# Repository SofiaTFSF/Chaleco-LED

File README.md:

# Chaleco-LED

## Presentación 
#### Integrantes
  -Carlos David Manzanares Medina.
  
  -Sofia Nuñez Montenegro.
#### Materia 
   -Taller de Electrónica
#### Profesor 
   -Johnny German Cubides Castro
   
## ¿Qué es?

Este chaleco es una ergonómica prenda la cual tiene integrada un sistema de luces la cual puedes ser modificada por medio de una aplicación que cumple la función de mando segun sea la necesidad del ciclista, ya sea que el usuario de la bicicleta gire, frene, o requiera de algun tipo de ayuda.

## Planteamiento del problema

En la actualidad, la ciudad de Bogotá experimenta lamentablemente una elevada incidencia de accidentes involucrando ciclistas. Estos incidentes de tránsito se atribuyen a diversas causas, siendo una de ellas la insuficiente comunicación entre los usuarios de la vía. Con el objetivo de mitigar esta problemática, se pretende concebir y desarrollar un chaleco dotado de un sistema de señalización direccional. Este dispositivo tiene como finalidad comunicar de manera efectiva las intenciones del ciclista a otros conductores, ya sea al realizar giros, frenar o requerir asistencia. La implementación de dicho sistema se llevará a cabo mediante la conectividad inalámbrica con dispositivos móviles.

## Objetivo

Nuestro objetivo principal es ayudar a que los ciclistas sean mas visibles en la vía minimizando así lo mayor posible los accidentes de los usuarios de este medio de transporte, este chaleco ayudará a que los ciclistas sean mas visibles especialmente en la noche por medio de un sistema de direccionales que permitirá comunicar los movimientos y prevenir cualquier inconveniente o accidente.

Se busca proporcionar información útil a otros conductores de vehiculos automatizados los cuales usan un sistema de señalización para indicar si voltean a la derecha, la izquierda o si están frenando, se incorporará este sistema por medio de un mando (aplicación) y un chaleco para ciclistas y así reducir los accidentes en la vía y por consiguiente reducir las muertes de ciclistas atropellados las cuales han aumentado en los últimos años.

Adicional a esto se espera promover el uso de la bicicleta como medio principal de transporte pues al mejorar la seguridad (unas de las razones por las cuales muchas personas no la usan) mas personas se sentiran atraidas por un medio de transporte que no solo mejorará su salud fisica y mental si no tambien ayudara a promover actos para preservar el medio ambiente, mitigando aunque sea un poco la emision dioxido de carbono.

## proceso

El primer paso en este proyecto consistió en identificar la problemática de los accidentes viales sufridos por ciclistas, particularmente debido a la colisión con vehículos automatizados, como automóviles, camionetas o autobuses. Con el objetivo de mitigar estos incidentes, se concibió la idea de incorporar un sistema de direccionales para permitir la comunicación entre ciclistas y la toma de decisiones anticipadas.

El proceso de desarrollo se centró en la creación de un diseño ergonómico que ofreciera comodidad a los ciclistas durante su manejo. Inicialmente, se abordó la implementación de luces, consideradas como un componente crucial para la visibilidad y seguridad. Estas luces fueron cortadas y conectadas de manera estratégica para alinearse con los conceptos y perspectivas de diseño, priorizando la excelencia tanto en estética como en la experiencia del usuario. La programación subsiguiente permitió que estas luces formaran símbolos legibles y universales para realizar señales claras.

El siguiente paso se enfocó en el diseño de la PCB (Placa de Circuito), que posibilitaría la desconexión de las luces de una fuente innamovible, garantizando así la movilidad del ciclista. La PCB incluye componentes como resistencias, el conector de luces, un jack, un microcontrolador (ESP32) y un portapilas. La fase de implementación abarcó la soldadura y conexión de los componentes, resolviendo eficientemente las posibles fallas presentadas durante este proceso. Este enfoque integral permitió avanzar de manera significativa hacia la materialización de una solución efectiva y segura para los ciclistas en el contexto del tráfico vial automatizado.

## Conclusiones 

Aunque el proceso no estuvo exento de desafíos, caracterizado por fluctuaciones y contratiempos, la culminación exitosa del proyecto se atribuye a diversos factores. La colaboración y orientación proporcionadas por el docente desempeñaron un papel fundamental, brindando dirección y apoyo técnico a lo largo de todas las etapas. Las herramientas facilitadas por el docente también desempeñaron un papel crucial al dotar al equipo de los recursos necesarios para abordar las complejidades del proyecto.

La resolución efectiva de problemas de última hora resultó ser un elemento determinante en el éxito final del emprendimiento. Este logro fue posible gracias al compromiso y dedicación de los miembros del equipo, quienes demostraron una actitud perseverante frente a los desafíos surgidos durante el desarrollo del chaleco funcional. La capacidad de adaptación y la disposición para superar obstáculos fueron cualidades clave que caracterizaron el desempeño del equipo.

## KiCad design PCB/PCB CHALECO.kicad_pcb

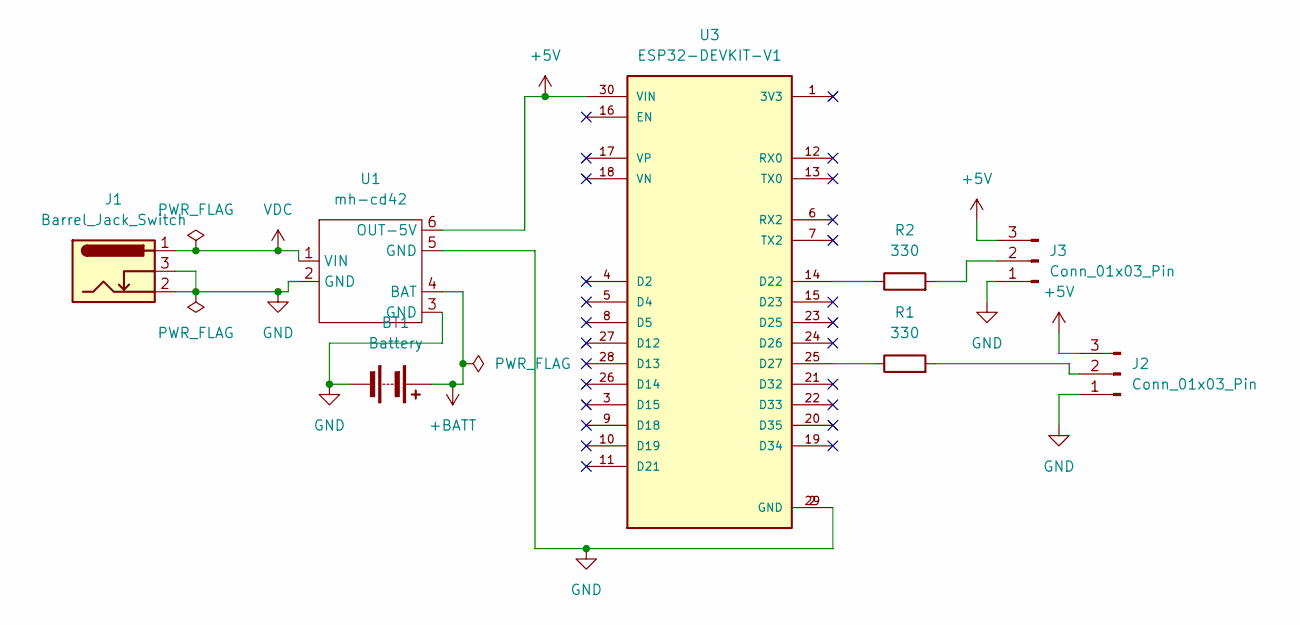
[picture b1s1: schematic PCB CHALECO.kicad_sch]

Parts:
BT1: Battery; BatteryHolder_MPD_BH-18650-PC2
J1: Barrel_Jack_Switch; BarrelJack_Horizontal
J2, J3: Conn_01x03_Pin; PinHeader_1x03_P2.54mm_Vertical
R1, R2: 330; R_Axial_DIN0204_L3.6mm_D1.6mm_P7.62mm_Horizontal
U1: mh-cd42
U3: ESP32-DEVKIT-V1; MODULE_ESP32_DEVKIT_V1; PARTREV N/A

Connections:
+5V: J2.3, J3.3, U1.6 (OUT-5V), U3.30 (VIN)
+BATT: BT1.1 (+), U1.4 (BAT)
GND: BT1.2 (-), J1.2, J1.3, J2.1, J3.1, U1.2 (GND), U1.3 (GND), U1.5 (GND), U3.2 (GND), U3.29 (GND)
unnamed: J2.2, R1.2
unnamed: J3.2, R2.2
unnamed: R2.1, U3.14 (D22)
unnamed: R1.1, U3.25 (D27)
VDC: J1.1, U1.1 (VIN)

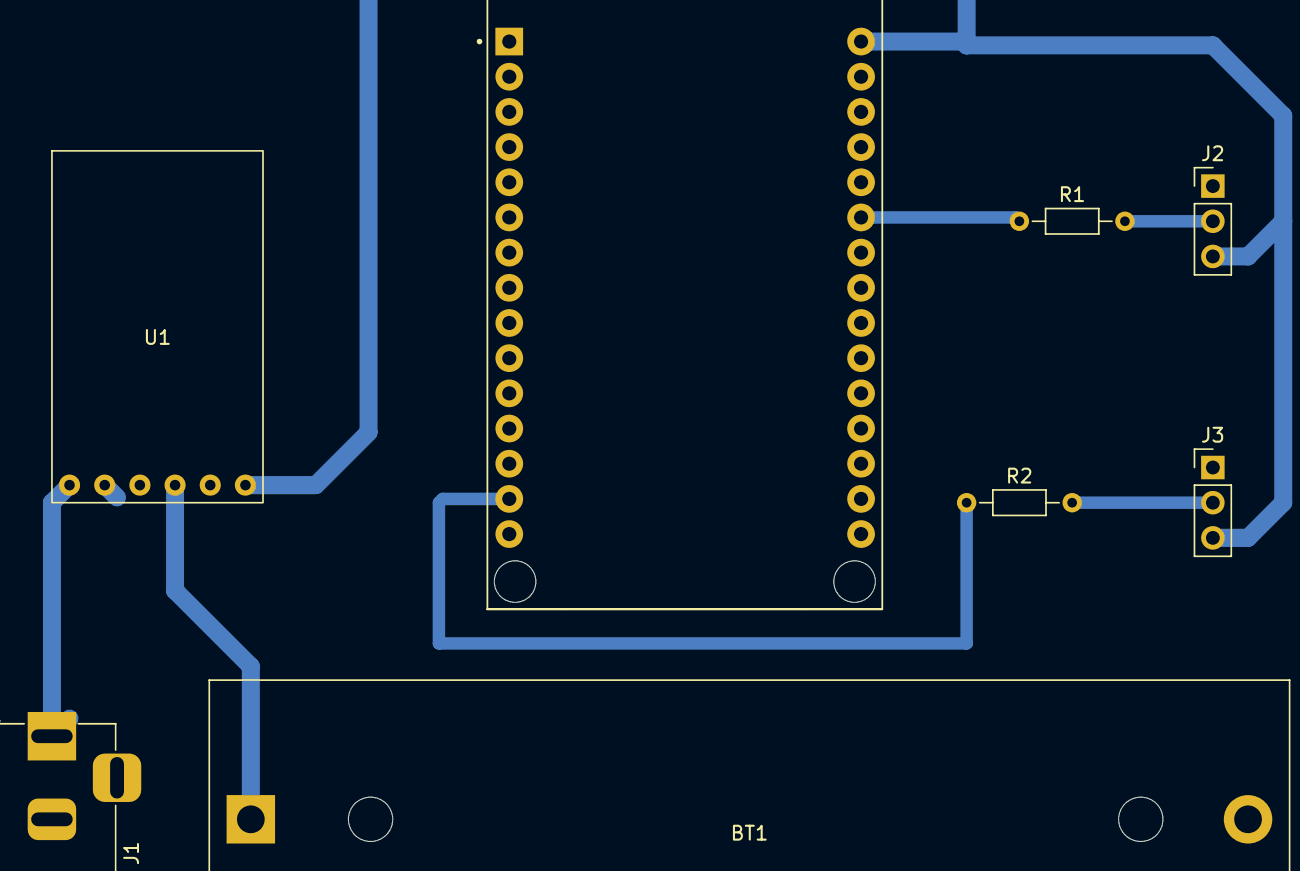
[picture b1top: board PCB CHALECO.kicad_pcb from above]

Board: 2 copper layers, 8 parts (0 on the bottom side), 8 nets.

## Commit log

2023-11-24 Create Ingenia Futuro
2023-11-24 Create Poster
2023-11-24 Create fotos
2023-11-24 Create s
2023-11-24 Update fotos
2023-11-24 Create f
2023-11-24 Create python
2023-11-24 Create Pcb
2023-11-24 Update Pcb
2023-11-28 Rename WifiAP.py to WifiAP
2023-11-28 Create WifiSTA
2023-12-01 Rename 1..jpeg to PROCESO DE SOLDADURA
2023-12-01 Rename python to main.py
2023-12-01 Rename WifiSTA to WifiSTA.py
2023-12-01 Rename WifiAP to WifiAP.py
2023-12-01 Rename fotos to READ.ME
2023-12-01 Create Luces festivas en el chaleco.
2023-12-01 Update and rename Luces festivas en el chaleco. to Videos
2023-12-01 Rename READ.ME to README.md
2023-12-01 Rename Videos to Videos.md
2023-12-01 Rename APP.jpeg to APP.md
2023-12-01 Rename Pcb to Pcb.mb
